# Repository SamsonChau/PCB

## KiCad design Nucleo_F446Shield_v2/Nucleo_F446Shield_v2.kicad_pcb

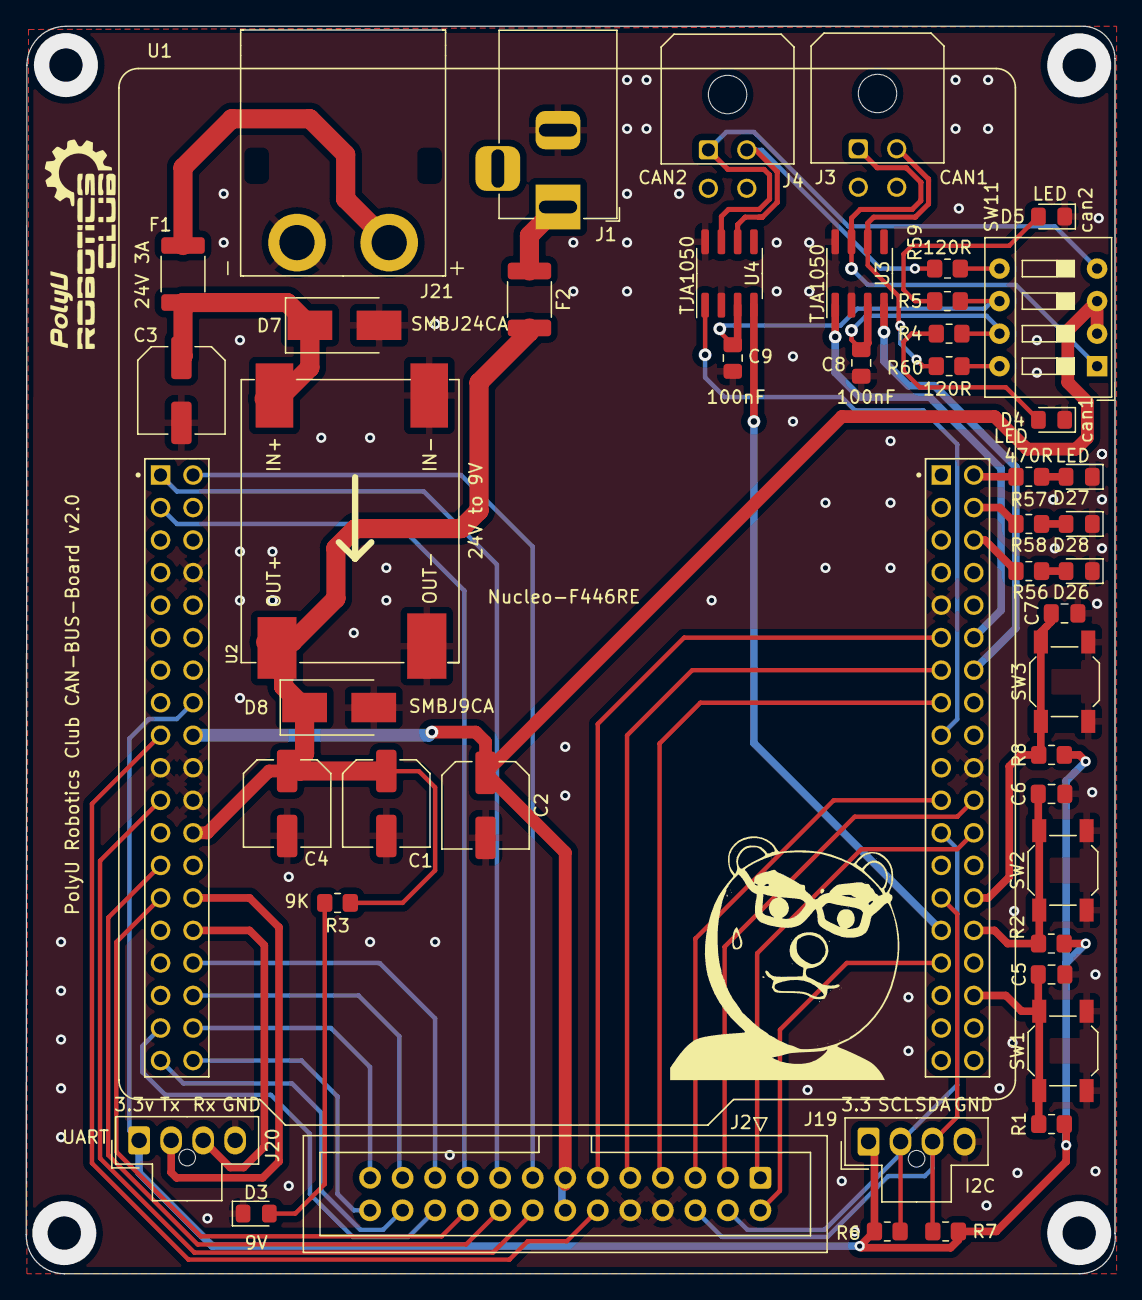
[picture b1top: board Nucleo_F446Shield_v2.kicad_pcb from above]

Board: 2 copper layers, 85.0 x 97.4 mm, 47 parts (0 on the bottom side), 55 nets.

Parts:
C1: 16v100uF; C_Elec_6.3x7.7
C2: 16v 47uF; C_Elec_6.3x7.7
C3: 35v 47uF; C_Elec_6.3x7.7
C4: 16v 100uF; C_Elec_6.3x7.7
C5, C6, C7, C8, C9: 100nF; C_0805_2012Metric_Pad1.18x1.45mm_HandSolder
D3: power_led; LED_0805_2012Metric_Pad1.15x1.40mm_HandSolder
D4: can_led; LED_0805_2012Metric_Pad1.15x1.40mm_HandSolder
D5: can2_led; LED_0805_2012Metric_Pad1.15x1.40mm_HandSolder
D7: SMBJ24CA; D_SMB_Handsoldering
D8: SMBJ9VCA; D_SMB_Handsoldering
D26: LED1; LED_0805_2012Metric_Pad1.15x1.40mm_HandSolder
D27: LED2; LED_0805_2012Metric_Pad1.15x1.40mm_HandSolder
D28: LED3; LED_0805_2012Metric_Pad1.15x1.40mm_HandSolder
F1, F2: 24V 3A; Fuse_1812_4532Metric_Pad1.30x3.40mm_HandSolder
J1: Barrel_Jack; BarrelJack_Horizontal
J2: Conn_02x13_Odd_Even; IDC-Header_2x13_P2.54mm_Vertical
J3: CAN1; Molex_Micro-Fit_3.0_43045-0400_2x02_P3.00mm_Horizontal
J4: CAN2; Molex_Micro-Fit_3.0_43045-0400_2x02_P3.00mm_Horizontal
J19: I2C3; Molex_Nano-Fit_105309-xx04_1x04_P2.50mm_Vertical
J20: UART4; Molex_Nano-Fit_105309-xx04_1x04_P2.50mm_Vertical
J21: xt60 male; XT60PW-M20
R1, R2, R8: 47k; R_0805_2012Metric_Pad1.20x1.40mm_HandSolder
R3, R4, R5: 10K; R_0805_2012Metric_Pad1.20x1.40mm_HandSolder
R6, R7: 4.7k; R_0805_2012Metric_Pad1.20x1.40mm_HandSolder
R56, R57, R58: 470R; R_0805_2012Metric_Pad1.20x1.40mm_HandSolder
R59, R60: 120R; R_0805_2012Metric_Pad1.20x1.40mm_HandSolder
SW1: SW1; SW_SPST_SKQG_WithoutStem
SW2: SW2; SW_SPST_SKQG_WithoutStem
SW3: SW3; SW_SPST_SKQG_WithoutStem
SW11: DIP1; SW_DIP_SPSTx04_Slide_9.78x12.34mm_W7.62mm_P2.54mm
U1: NUCLEO-F446RE
U2: MP1584; DC-DC-mp1584_module
U3, U4: TJA1050; SOIC-8_3.9x4.9mm_P1.27mm

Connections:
+3V3: J19.1, J20.1, R1.2, R2.2, R6.1, R7.1, R8.2, U1.CN7_16 (CN7_+3V3)
+5V: C2.1, J2.13, J2.14, SW11.2, SW11.3, U1.CN7_18 (CN7_+5V)
+24V: F1.1, J21.2
/CAN1+: J3.1, SW11.1, U3.7 (CANH)
/CAN1-: J3.2, R60.2, U3.6 (CANL)
/CAN1_VCC: C8.1, R4.1, SW11.7, U3.3 (VDD)
/CAN2+: J4.1, SW11.4, U4.7 (CANH)
/CAN2-: J4.2, R59.2, U4.6 (CANL)
/CAN2_VCC: C9.1, R5.1, SW11.6, U4.3 (VDD)
/PA0: J20.2, U1.CN7_28 (PA0)
/PA1: J20.3, U1.CN7_30 (PA1)
/PA8: J2.4, J19.2, R6.2, U1.CN10_23 (PA8)
/PA11: U1.CN10_14 (PA11), U3.4 (RXD)
/PA12: U1.CN10_12 (PA12), U3.1 (TXD)
/PB4: J2.6, J19.3, R7.2, U1.CN10_27 (PB4)
/PB5: U1.CN10_29 (PB5), U4.4 (RXD)
/PB6: U1.CN10_17 (PB6), U4.1 (TXD)
/PB13: C6.1, R2.1, SW2.2, U1.CN10_30 (PB13)
/PB14: C7.1, R8.1, SW3.2, U1.CN10_28 (PB14)
/PC4: C5.1, R1.1, SW1.2, U1.CN10_34 (PC4)
/PC5: R56.1, U1.CN10_6 (PC5)
/PC6: R58.1, U1.CN10_4 (PC6)
/PC8: R57.1, U1.CN10_2 (PC8)
GND: C1.2, C2.2, C3.2, C4.2, C5.2, C6.2, C7.2, C8.2, C9.2, D3.1 (K), D4.1 (K), D5.1 (K), D7.2 (A), D8.2 (A), D26.1 (K), D27.1 (K), D28.1 (K), J1.2, J2.8, J2.10, J19.4, J20.4, J21.1, SW1.1, SW2.1, SW3.1, U1.CN7_8 (CN7_GND), U1.CN7_19 (CN7_GND), U1.CN7_20 (CN7_GND), U1.CN7_22 (CN7_GND), U1.CN10_9 (CN10_GND), U1.CN10_20 (CN10_GND), U2.IN2- (VIN-), U2.OUT2- (VOUT-), U3.2 (VSS), U3.8 (Rs), U4.2 (VSS), U4.8 (Rs)
unnamed: C3.1, D7.1 (K), F1.2, U2.IN1+ (VIN+)
unnamed: D3.2 (A), R3.2
unnamed: D4.2 (A), R4.2
unnamed: D5.2 (A), R5.2
unnamed: D26.2 (A), R56.2
unnamed: D27.2 (A), R57.2
unnamed: D28.2 (A), R58.2
unnamed: F2.1, J1.1
unnamed: R59.1, SW11.5
unnamed: R60.1, SW11.8
PA4: J2.21, U1.CN7_32 (PA4)
PA5: J2.11, U1.CN10_11 (PA5)
PA6: J2.9, U1.CN10_13 (PA6)
PA7: J2.7, U1.CN10_15 (PA7)
PA9: J2.5, U1.CN10_21 (PA9)
PA15: J2.12, U1.CN7_17 (PA15)
PB0: J2.23, U1.CN7_34 (PB0)
PB1: J2.1, U1.CN10_24 (PB1)
PB2: J2.3, U1.CN10_22 (PB2)
PB3: J2.2, U1.CN10_31 (PB3)
PB7: J2.16, U1.CN7_21 (PB7)
PC0: J2.26, U1.CN7_38 (PC0/PB8)
PC1: J2.25, U1.CN7_36 (PC1/PB9)
PC2: J2.22, U1.CN7_35 (PC2)
PC3: J2.24, U1.CN7_37 (PC3)
PC10: J2.17, U1.CN7_1 (PC10)
PC11: J2.15, U1.CN7_2 (PC11)
PC12: J2.19, U1.CN7_3 (PC12)
PC14: J2.18, U1.CN7_25 (PC14)
PC15: J2.20, U1.CN7_27 (PC15)
VCC: C1.1, C4.1, D8.1 (K), F2.2, R3.1, U1.CN7_24 (CN7_VIN), U2.OUT1+ (VOUT+)

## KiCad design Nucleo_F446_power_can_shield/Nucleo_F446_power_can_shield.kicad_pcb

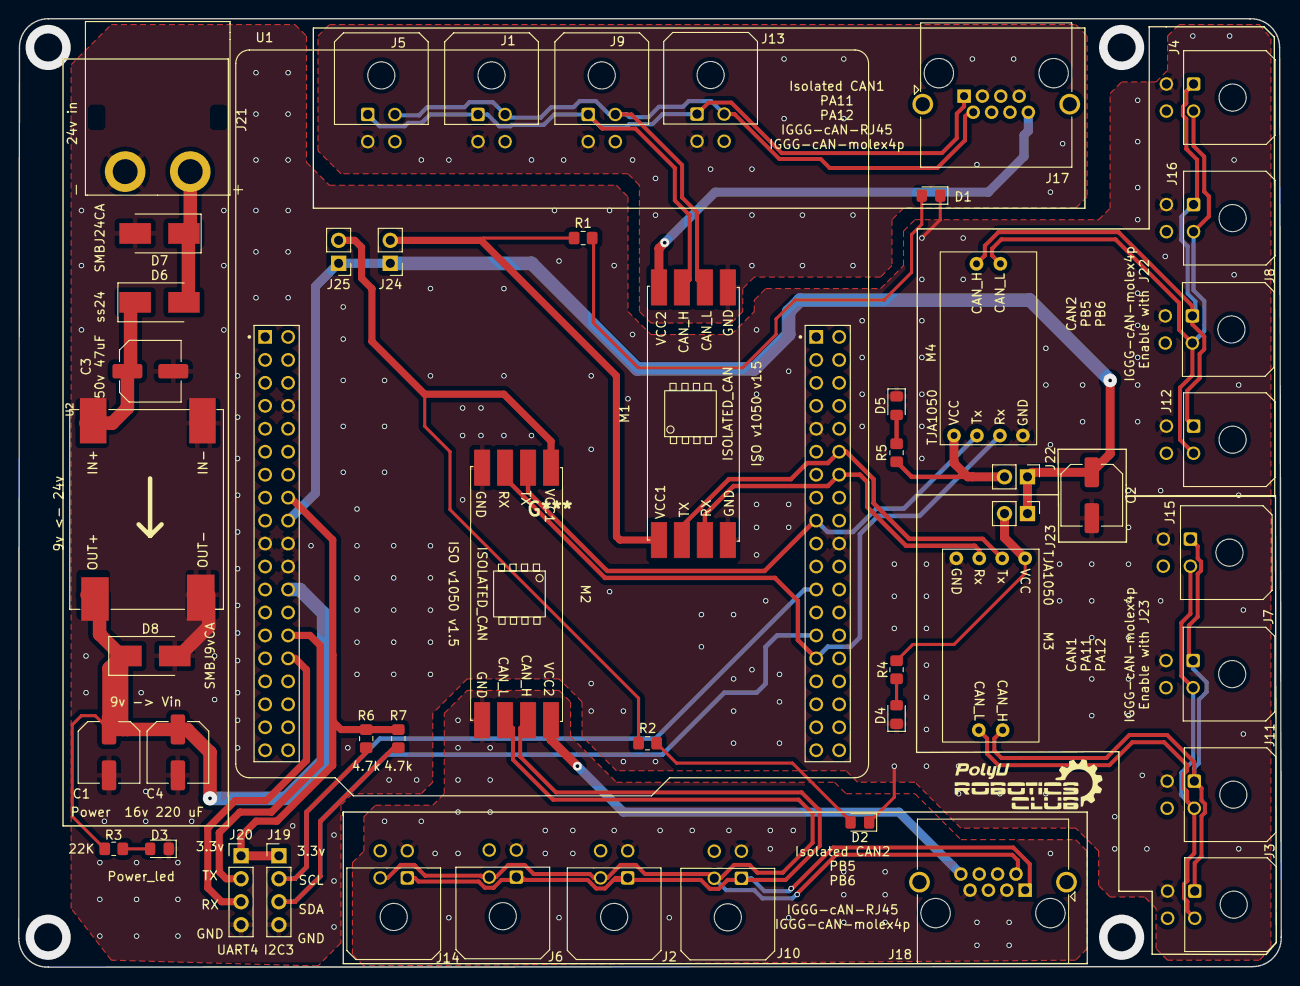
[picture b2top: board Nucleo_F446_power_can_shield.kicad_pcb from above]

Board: 2 copper layers, 139.7 x 104.9 mm, 50 parts (0 on the bottom side), 34 nets.

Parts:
C1: 16v220uF; C_Elec_6.3x7.7
C2, C4: 16v 220uF; C_Elec_6.3x7.7
C3: 50v 47uF; C_Elec_6.3x7.7
D1, D2, D4, D5: can_led; LED_0805_2012Metric_Pad1.15x1.40mm_HandSolder
D3: power_led; LED_0805_2012Metric_Pad1.15x1.40mm_HandSolder
D6: ss24; D_SMB_Handsoldering
D7: SMBJ24CA; D_SMB_Handsoldering
D8: SMBJ9VCA; D_SMB_Handsoldering
J1, J5, J9, J13: ISOCAN1; Molex_Micro-Fit_3.0_43045-0400_2x02_P3.00mm_Horizontal
J2, J6, J10, J14: ISOCAN2; Molex_Micro-Fit_3.0_43045-0400_2x02_P3.00mm_Horizontal
J3, J7, J11, J15: CAN1; Molex_Micro-Fit_3.0_43045-0400_2x02_P3.00mm_Horizontal
J4, J8, J12, J16: CAN2; Molex_Micro-Fit_3.0_43045-0400_2x02_P3.00mm_Horizontal
J17, J18: RJ45; RJ45_Amphenol_RJHSE5380
J19: I2C3; PinHeader_1x04_P2.54mm_Vertical
J20: UART4; PinHeader_1x04_P2.54mm_Vertical
J21: xt60 male; XT60PW-M20
J22, J23, J24, J25: enable; PinHeader_1x02_P2.54mm_Vertical
M1, M2: Isolated-Can-Transceiver-Module-ISO1050-Module
M3, M4: TJA1050_Module; TJA1050_CAN_Module
R1, R2, R4, R5: 10K; R_0805_2012Metric_Pad1.20x1.40mm_HandSolder
R3: 22K; R_0805_2012Metric_Pad1.20x1.40mm_HandSolder
R6, R7: 4.7k; R_0805_2012Metric_Pad1.20x1.40mm_HandSolder
U1: NUCLEO-F446RE
U2: MP1584; DC-DC-mp1584_module

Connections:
+3V3: J19.1, J20.1, R6.1, R7.1, U1.CN7_16 (CN7_+3V3)
+5V: C2.1, J22.1, J23.1, J24.1, J25.1, U1.CN7_18 (CN7_+5V)
+24V: D6.2 (A), D7.1 (K), J21.2
/CAN1+: J3.1, J7.1, J11.1, J15.1, M3.5 (CAN_H)
/CAN1-: J3.2, J7.2, J11.2, J15.2, M3.6 (CAN_L)
/CAN2+: J4.1, J8.1, J12.1, J16.1, M4.5 (CAN_H)
/CAN2-: J4.2, J8.2, J12.2, J16.2, M4.6 (CAN_L)
/ISO-CAN1+: J1.1, J5.1, J9.1, J13.1, J17.1, M1.6 (CAN_H)
/ISO-CAN1-: J1.2, J5.2, J9.2, J13.2, J17.2, M1.7 (CAN_L)
/ISO-CAN2+: J2.1, J6.1, J10.1, J14.1, J18.1, M2.6 (CAN_H)
/ISO-CAN2-: J2.2, J6.2, J10.2, J14.2, J18.2, M2.7 (CAN_L)
/PA0: J20.2, U1.CN7_28 (PA0)
/PA1: J20.3, U1.CN7_30 (PA1)
/PA8: J19.2, R6.2, U1.CN10_23 (PA8)
/PA11: M1.3 (RX), M3.3 (RX), U1.CN10_14 (PA11)
/PA12: M1.2 (TX), M3.2 (TX), U1.CN10_12 (PA12)
/PB4: J19.3, R7.2, U1.CN10_27 (PB4)
/PB5: M2.3 (RX), M4.3 (RX), U1.CN10_29 (PB5)
/PB6: M2.2 (TX), M4.2 (TX), U1.CN10_17 (PB6)
<NO NET>: J17.8, J18.8, M1.5 (VCC2), M2.5 (VCC2)
GND: C1.2, C2.2, C3.2, C4.2, D1.1 (K), D2.1 (K), D3.1 (K), D4.1 (K), D5.1 (K), D7.2 (A), D8.2 (A), J3.3, J4.3, J7.3, J8.3, J11.3, J12.3, J15.3, J16.3, J19.4, J20.4, J21.1, M1.4 (GND1), M2.4 (GND1), M3.4 (GND), M4.4 (GND), U1.CN7_8 (CN7_GND), U1.CN7_19 (CN7_GND), U1.CN7_20 (CN7_GND), U1.CN7_22 (CN7_GND), U1.CN10_9 (CN10_GND), U1.CN10_20 (CN10_GND), U2.IN2- (VIN-), U2.OUT2- (VOUT-)
GND1: J1.3, J5.3, J9.3, J13.3, J17.3, J17.7, M1.8 (GND2)
GND2: J2.3, J6.3, J10.3, J14.3, J18.3, J18.7, M2.8 (GND2)
unnamed: C3.1, D6.1 (K), U2.IN1+ (VIN+)
unnamed: D1.2 (A), R1.2
unnamed: D2.2 (A), R2.2
unnamed: D3.2 (A), R3.2
unnamed: D4.2 (A), R4.2
unnamed: D5.2 (A), R5.2
unnamed: J22.2, M4.1 (VCC), R5.1
unnamed: J23.2, M3.1 (VCC), R4.1
unnamed: J24.2, M1.1 (VCC1), R1.1
unnamed: J25.2, M2.1 (VCC1), R2.1
VCC: C1.1, C4.1, D8.1 (K), R3.1, U1.CN7_24 (CN7_VIN), U2.OUT1+ (VOUT+)

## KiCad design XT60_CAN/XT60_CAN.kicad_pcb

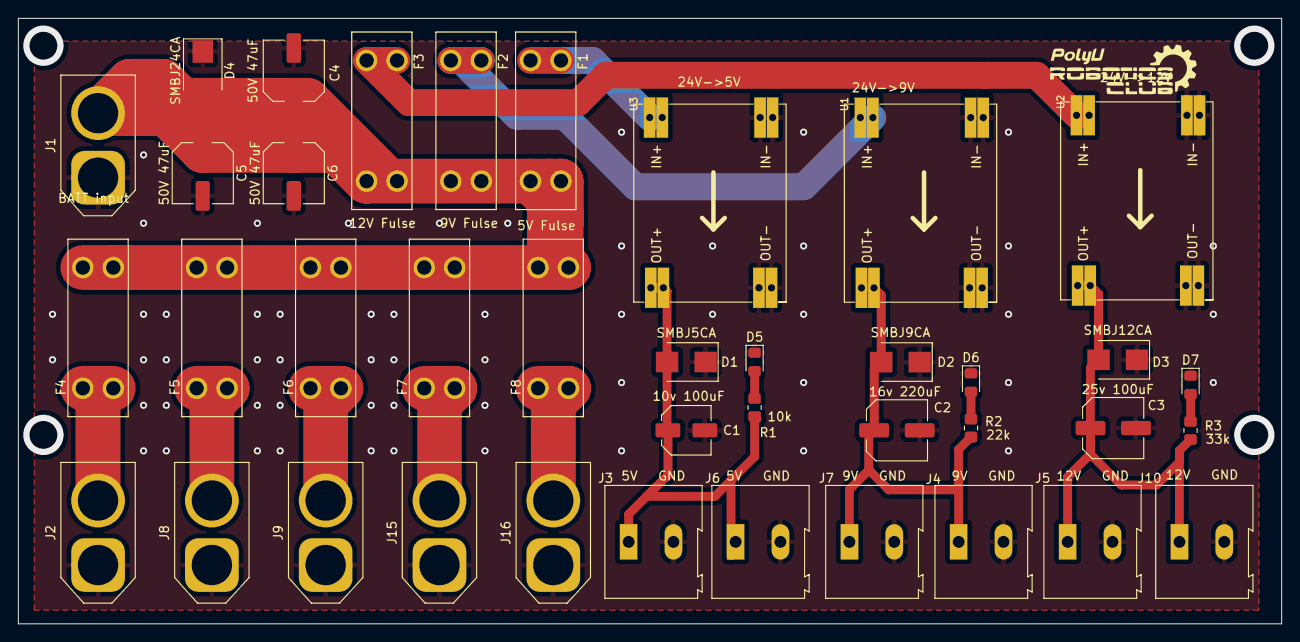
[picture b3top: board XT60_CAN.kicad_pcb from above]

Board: 2 copper layers, 141.0 x 67.6 mm, 39 parts (0 on the bottom side), 16 nets.

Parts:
C1: 10v 100uF; C_Elec_5x5.4
C2: 16v 220uF; C_Elec_6.3x7.7
C3: 25v 100uF; C_Elec_6.3x7.7
C4, C5, C6: 50v 47uF; C_Elec_6.3x7.7
D1: SMBJ5CA; D_SMB
D2: SMBJ9CA; D_SMB
D3: SMBJ12CA; D_SMB
D4: SMBJ24CA; D_SMB
D5: 5v_led; LED_0805_2012Metric_Pad1.15x1.40mm_HandSolder
D6: 9v_led; LED_0805_2012Metric_Pad1.15x1.40mm_HandSolder
D7: 12v_led; LED_0805_2012Metric_Pad1.15x1.40mm_HandSolder
F1, F2, F3, F4, F5, F6, F7, F8: 3557-2; FUSE_3557-2
J1: XT60_IN; AMASS_XT60-M_1x02_P7.20mm_Vertical
J2: XT60_CH1; AMASS_XT60-F_1x02_P7.20mm_Vertical
J3, J6: +5v; TerminalBlock_Altech_AK300-2_P5.00mm
J4, J7: +9v; TerminalBlock_Altech_AK300-2_P5.00mm
J5, J10: +12v; TerminalBlock_Altech_AK300-2_P5.00mm
J8: XT60_CH2; AMASS_XT60-F_1x02_P7.20mm_Vertical
J9: XT60_CH3; AMASS_XT60-F_1x02_P7.20mm_Vertical
J15: XT60_CH4; AMASS_XT60-F_1x02_P7.20mm_Vertical
J16: XT60_CH5; AMASS_XT60-F_1x02_P7.20mm_Vertical
R1: 10k; R_0805_2012Metric_Pad1.20x1.40mm_HandSolder
R2: 22k; R_0805_2012Metric_Pad1.20x1.40mm_HandSolder
R3: 33k; R_0805_2012Metric_Pad1.20x1.40mm_HandSolder
U1, U2, U3: MP1584; DC-DC-mp1584_module

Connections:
+5V: C1.1, D1.2 (A2), J3.1, J6.1, R1.1, U3.OUT1+ (VOUT+), U3.OUT2+ (VOUT+)
+9V: C2.1, D2.2 (A2), J4.1, J7.1, R2.1, U1.OUT1+ (VOUT+), U1.OUT2+ (VOUT+)
+12V: C3.1, D3.2 (A2), J5.1, J10.1, R3.1, U2.OUT1+ (VOUT+), U2.OUT2+ (VOUT+)
+24V: C4.1, C5.1, C6.1, D4.2 (A2), F1.2, F2.2, F3.2, F4.2, F5.2, F6.2, F7.2, F8.2, J1.2
GND: C1.2, C2.2, C3.2, C4.2, C5.2, C6.2, D1.1 (A1), D2.1 (A1), D3.1 (A1), D4.1 (A1), D5.1 (K), D6.1 (K), D7.1 (K), J1.1, J2.1, J3.2, J4.2, J5.2, J6.2, J7.2, J8.1, J9.1, J10.2, J15.1, J16.1, U1.IN1- (VIN-), U1.IN2- (VIN-), U1.OUT1- (VOUT-), U1.OUT2- (VOUT-), U2.IN1- (VIN-), U2.IN2- (VIN-), U2.OUT1- (VOUT-), U2.OUT2- (VOUT-), U3.IN1- (VIN-), U3.IN2- (VIN-), U3.OUT1- (VOUT-), U3.OUT2- (VOUT-)
unnamed: D5.2 (A), R1.2
unnamed: D6.2 (A), R2.2
unnamed: D7.2 (A), R3.2
unnamed: F1.1, U3.IN1+ (VIN+), U3.IN2+ (VIN+)
unnamed: F2.1, U1.IN1+ (VIN+), U1.IN2+ (VIN+)
unnamed: F3.1, U2.IN1+ (VIN+), U2.IN2+ (VIN+)
unnamed: F4.1, J2.2
unnamed: F5.1, J8.2
unnamed: F6.1, J9.2
unnamed: F7.1, J15.2
unnamed: F8.1, J16.2

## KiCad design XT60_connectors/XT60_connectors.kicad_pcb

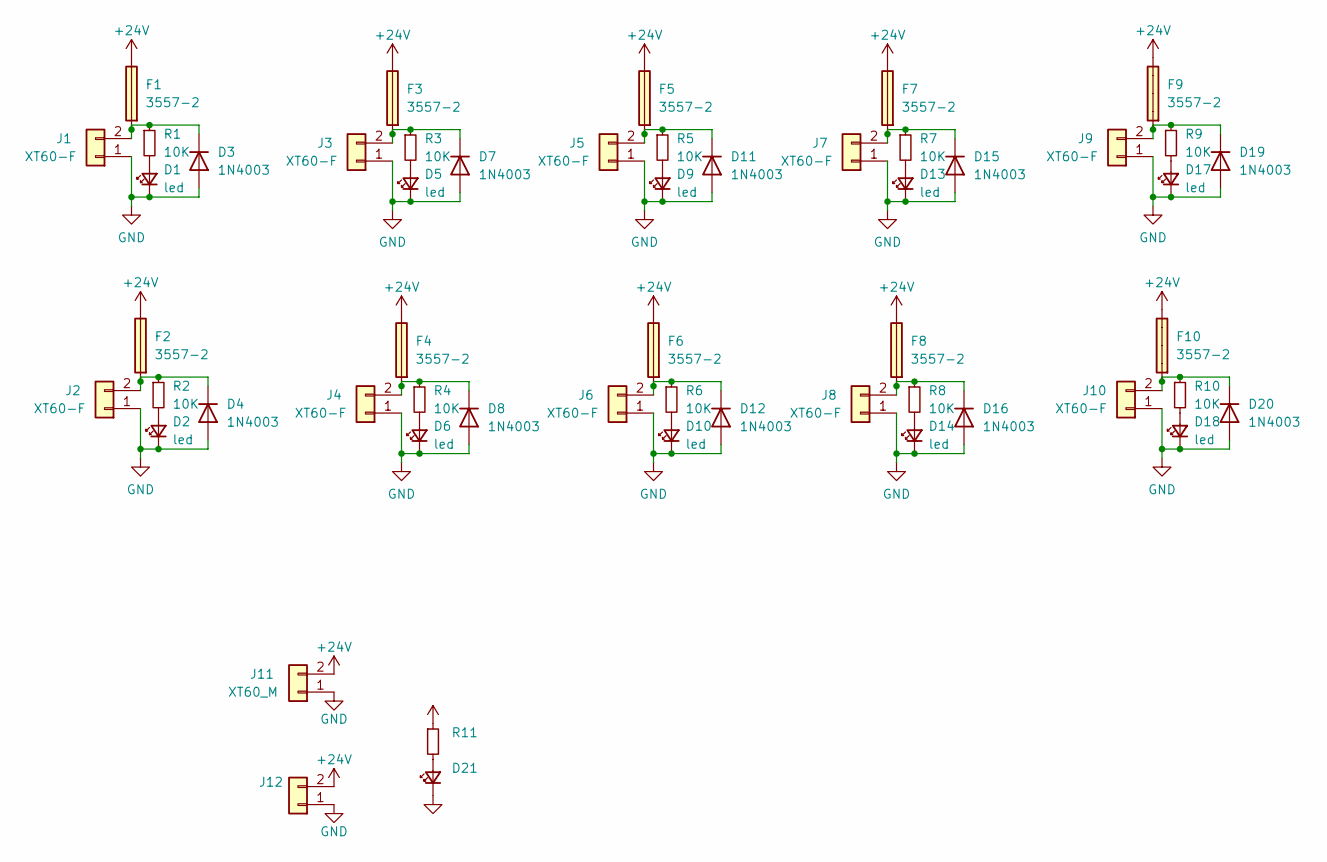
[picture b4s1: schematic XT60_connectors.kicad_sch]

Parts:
D1, D2, D5, D6, D9, D10, D13, D14, D17, D18: led; LED_0805_2012Metric_Pad1.15x1.40mm_HandSolder
D3, D4, D7, D8, D11, D12, D15, D16, D19, D20: 1N4003; D_DO-41_SOD81_P10.16mm_Horizontal
D21: (no value)
F1, F2, F3, F4, F5, F6, F7, F8, F9, F10: 3557-2; FUSE_3557-2
J1, J2, J3, J4, J5, J6, J7, J8, J9, J10: XT60-F; AMASS_XT60-F_1x02_P7.20mm_Vertical
J11: XT60_M; AMASS_XT60-M_1x02_P7.20mm_Vertical
J12: (no value)
R1, R2, R3, R4, R5, R6, R7, R8, R9, R10: 10K; R_0805_2012Metric_Pad1.20x1.40mm_HandSolder
R11: (no value)

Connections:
unnamed: D1.2 (A), R1.2
unnamed: D2.2 (A), R2.2
unnamed: D3.1 (K), F1.1, J1.2, R1.1
unnamed: D4.1 (K), F2.1, J2.2, R2.1
unnamed: D5.2 (A), R3.2
unnamed: D6.2 (A), R4.2
unnamed: D7.1 (K), F3.1, J3.2, R3.1
unnamed: D8.1 (K), F4.1, J4.2, R4.1
unnamed: D9.2 (A), R5.2
unnamed: D10.2 (A), R6.2
unnamed: D11.1 (K), F5.1, J5.2, R5.1
unnamed: D12.1 (K), F6.1, J6.2, R6.1
unnamed: D13.2 (A), R7.2
unnamed: D14.2 (A), R8.2
unnamed: D15.1 (K), F7.1, J7.2, R7.1
unnamed: D16.1 (K), F8.1, J8.2, R8.1
unnamed: D17.2 (A), R9.2
unnamed: D18.2 (A), R10.2
unnamed: D19.1 (K), F9.1, J9.2, R9.1
unnamed: D20.1 (K), F10.1, J10.2, R10.1
unnamed: D21.2 (A), R11.2

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
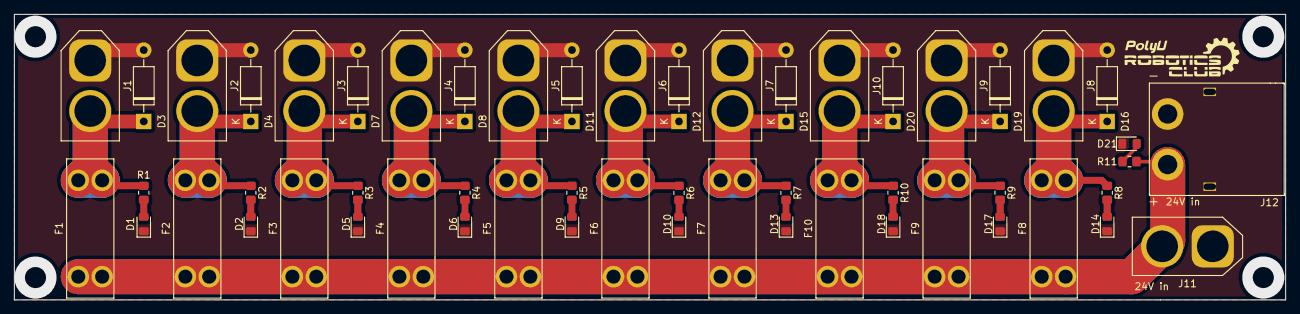
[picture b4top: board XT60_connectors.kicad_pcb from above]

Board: 2 copper layers, 181.0 x 40.6 mm, 54 parts (0 on the bottom side), 23 nets.

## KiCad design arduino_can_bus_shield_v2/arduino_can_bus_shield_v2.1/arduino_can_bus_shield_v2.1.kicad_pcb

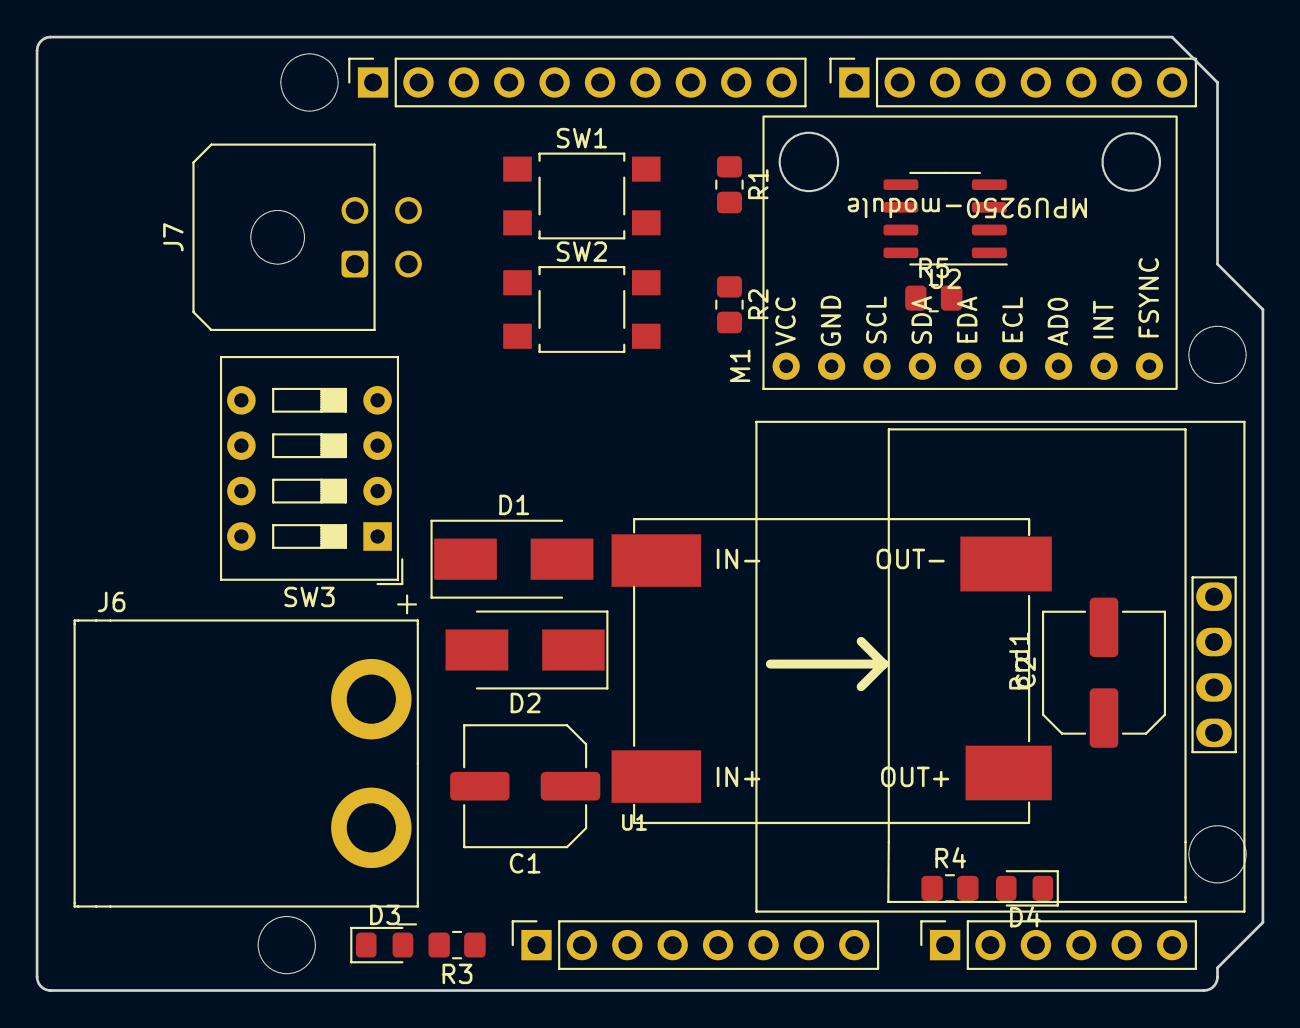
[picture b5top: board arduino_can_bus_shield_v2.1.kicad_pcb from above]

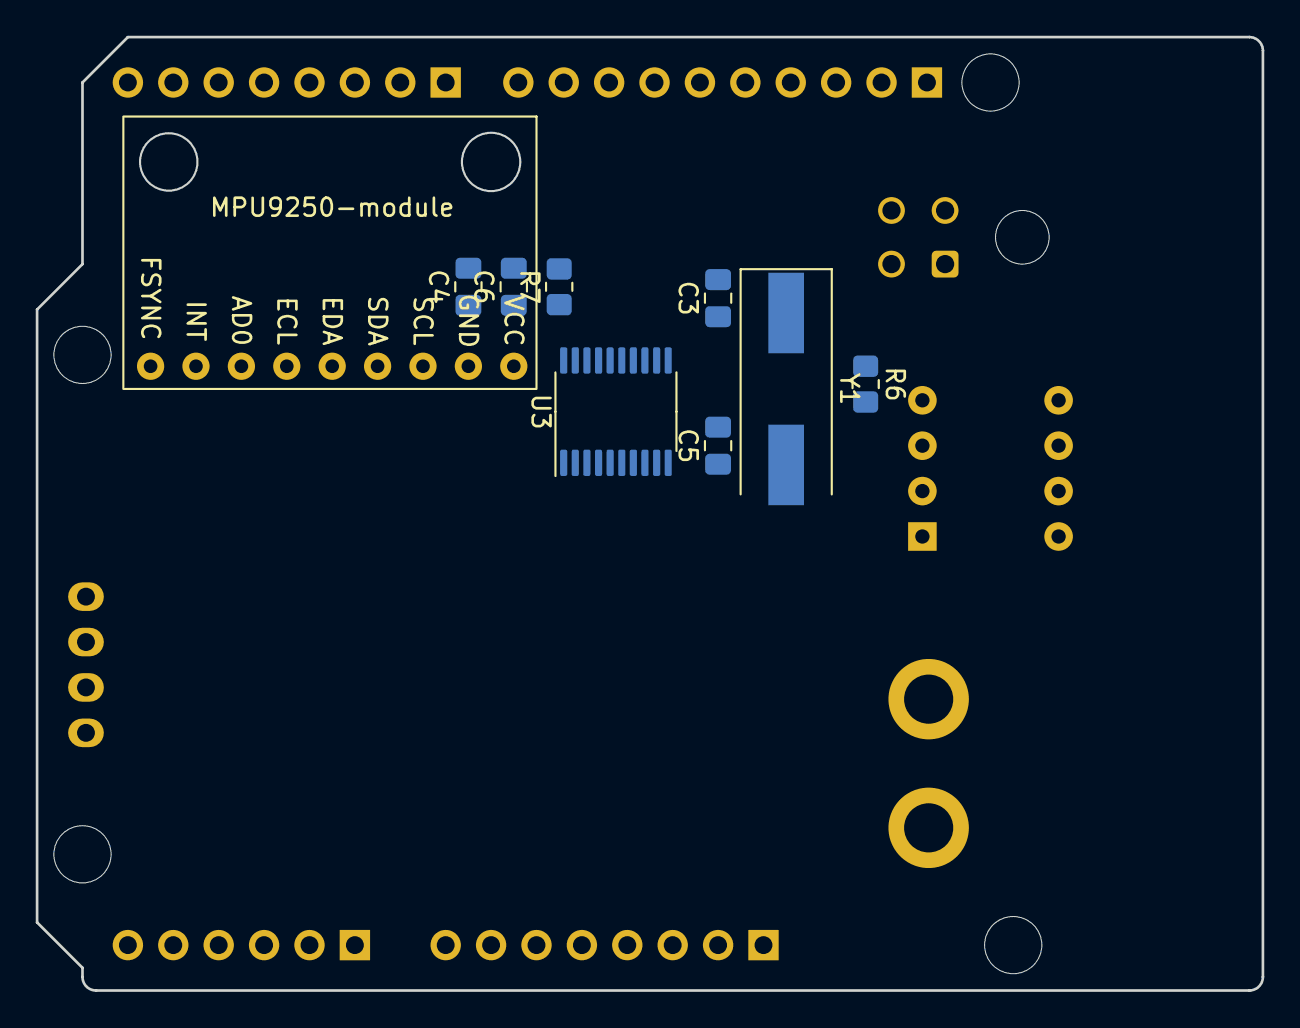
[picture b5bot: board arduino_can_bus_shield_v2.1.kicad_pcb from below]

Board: 2 copper layers, 68.6 x 53.3 mm, 36 parts (8 on the bottom side), 27 nets, no tracks yet.

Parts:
Brd1: SSD1306; 128x64OLED
C1: 50v 47uF; C_Elec_6.3x7.7
C2: 16v 220uF; C_Elec_6.3x7.7
C3, C5: 22pF; C_0805_2012Metric_Pad1.18x1.45mm_HandSolder
C4, C6: 100nF; C_0805_2012Metric_Pad1.18x1.45mm_HandSolder
D1: SMBJ24CA; D_SMB_Handsoldering
D2: ss24; D_SMB_Handsoldering
D3: power; LED_0805_2012Metric_Pad1.15x1.40mm_HandSolder
D4: user; LED_0805_2012Metric_Pad1.15x1.40mm_HandSolder
J1: Power; PinSocket_1x08_P2.54mm_Vertical
J2: Digital/PWM; PinSocket_1x10_P2.54mm_Vertical
J3: Analog; PinSocket_1x06_P2.54mm_Vertical
J4: Digital/PWM; PinSocket_1x08_P2.54mm_Vertical
J6: xt60 male; XT60PW-M20
J7: molex_3.0; Molex_Micro-Fit_3.0_43045-0400_2x02_P3.00mm_Horizontal
M1: MPU9250_module
MH1, MH2, MH3, MH4: MountingHole_3.2mm
R1, R2, R3, R4, R7: 10K; R_0805_2012Metric_Pad1.20x1.40mm_HandSolder
R5: 17K; R_0805_2012Metric_Pad1.20x1.40mm_HandSolder
R6: 120; R_0805_2012Metric_Pad1.20x1.40mm_HandSolder
SW1: User; SW_SPST_TL3305A
SW2: User; SW_SPST_TL3305C
SW3: SW_DIP_x04; SW_DIP_SPSTx04_Slide_9.78x12.34mm_W7.62mm_P2.54mm
U1: MP1584; DC-DC-mp1584_module
U2: MCP2551-I-SN; SOIC-8_3.9x4.9mm_P1.27mm
U3: MCP2515-xST; TSSOP-20_4.4x6.5mm_P0.65mm
Y1: 16MHz; Crystal_SMD_HC49-SD

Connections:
+5V: J1.5, R3.1, R7.1, SW1.2, SW2.2, SW3.1, SW3.2
+24V: D1.1 (K), D2.2 (A), J6.2
/7: J4.1, U3.18 (~CS)
/8: J2.10, R2.1, SW2.1
/9(**): R1.1, SW1.1
/A0: J3.1, R4.1
/A4(SDA): Brd1.4 (SDA), M1.3 (SDA)
/A5(SCL): Brd1.3 (SCL), M1.2 (SCL)
/CAN+: J7.1, R6.1, U2.7 (CANH)
/CAN-: J7.2, SW3.5, U2.6 (CANL)
/CAN_Rx: U2.4 (RXD), U3.2 (RXCAN)
/CAN_Tx: U2.1 (TXD), U3.1 (TXCAN)
/SCL/A5: J2.1, J3.6
/SDA/A4: J2.2, J3.5
/can_enable: C4.1, C6.1, SW3.8, U2.3 (VDD), U3.20 (VDD)
/imu_enable: M1.0 (VCC), SW3.7
GND: Brd1.1 (GND), C1.2, C2.2, C3.2, C4.2, C5.2, C6.2, D1.2 (A), D3.1 (K), D4.1 (K), J1.6, J1.7, J2.4, J6.1, M1.1 (GND), R1.2, R2.2, R5.2, SW3.6, U1.IN2- (VIN-), U1.OUT2- (VOUT-), U2.2 (VSS), U3.10 (VSS)
unnamed: C1.1, D2.1 (K), U1.IN2+ (VIN+)
unnamed: C3.1, U3.8 (OSC2), Y1.1
unnamed: C5.1, U3.9 (OSC1), Y1.2
unnamed: D3.2 (A), R3.2
unnamed: D4.2 (A), R4.2
unnamed: J7.3, SW3.3
unnamed: R5.1, U2.8 (Rs)
unnamed: R6.2, SW3.4
unnamed: R7.2, U3.19 (~RESET)
VCC: C2.1, J1.8, U1.OUT2+ (VOUT+)

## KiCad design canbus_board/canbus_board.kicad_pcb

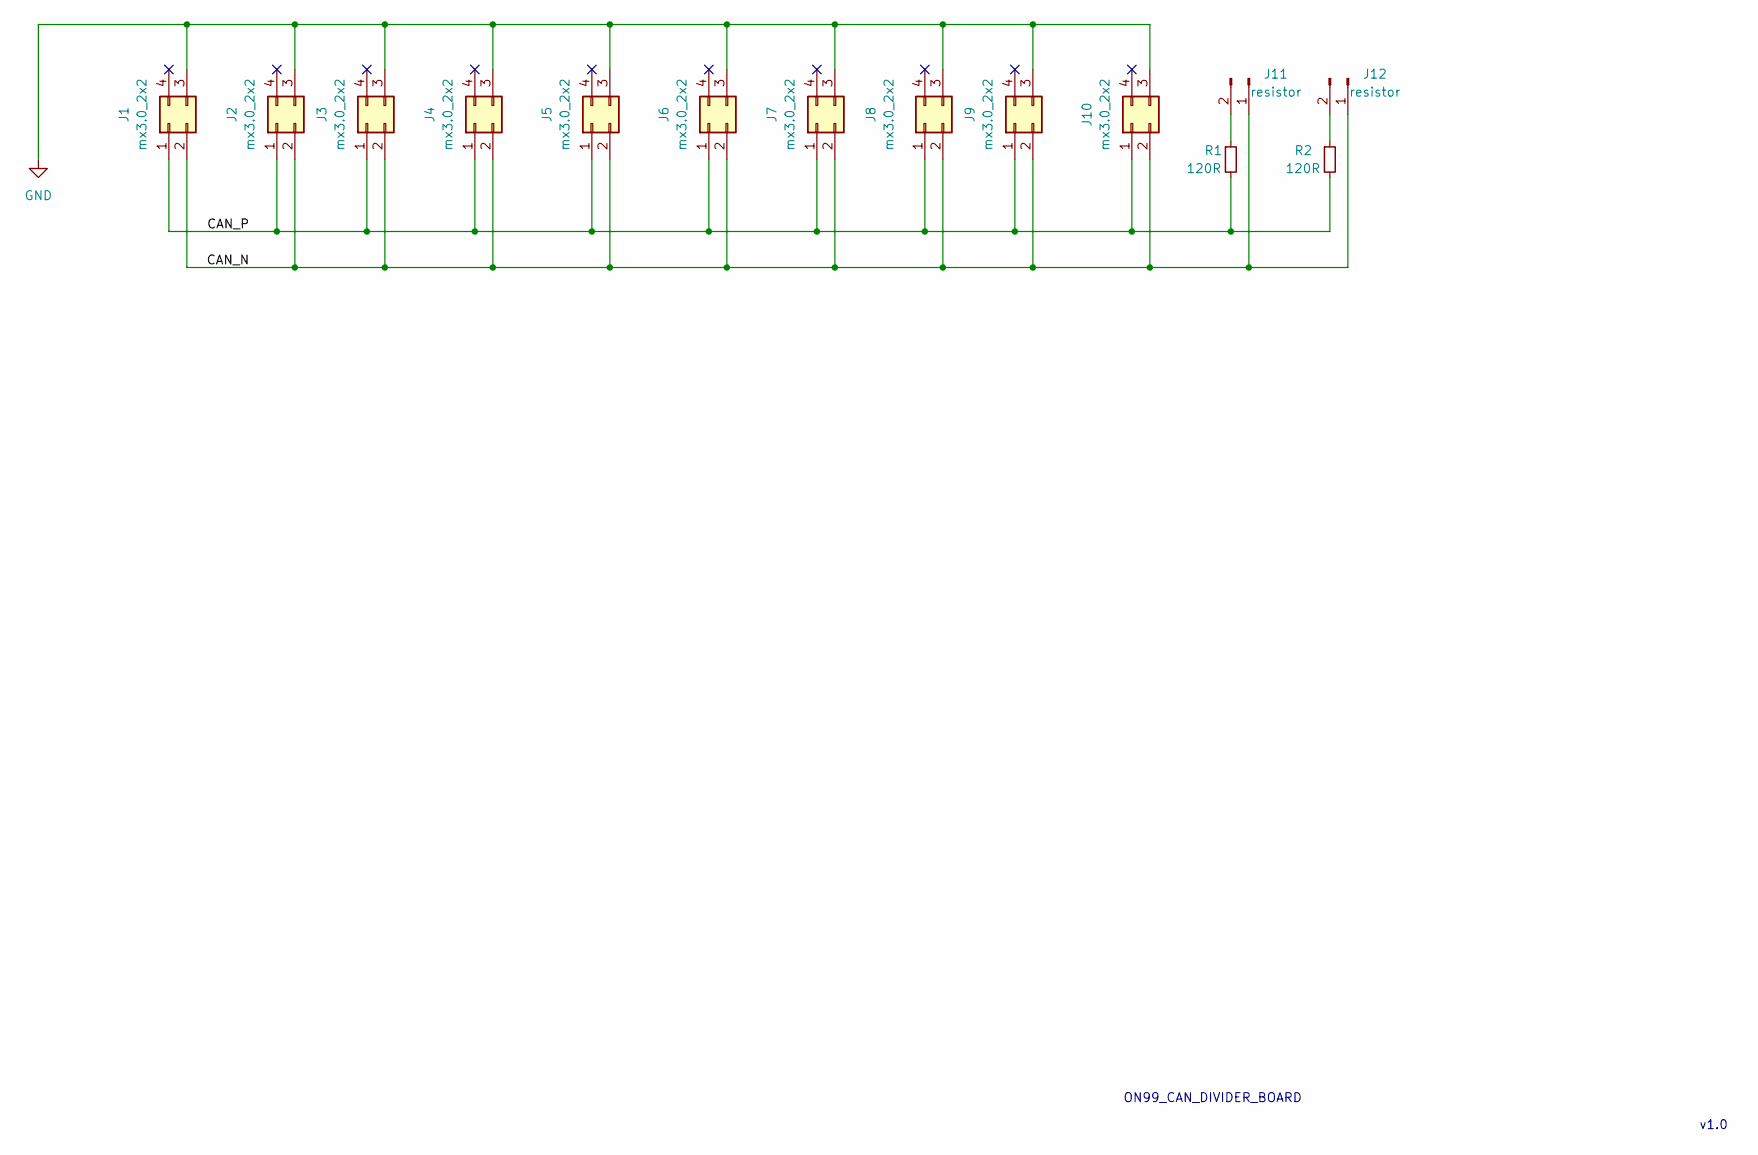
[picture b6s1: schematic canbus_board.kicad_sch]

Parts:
J1, J2, J3, J4, J5, J6, J7, J8, J9, J10: mx3.0_2x2; Molex_Micro-Fit_3.0_43045-0412_2x02_P3.00mm_Vertical
J11, J12: resistor; PinHeader_1x02_P2.54mm_Vertical
R1, R2: 120R; R_0805_2012Metric_Pad1.20x1.40mm_HandSolder

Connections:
/CAN_N: J1.2, J2.2, J3.2, J4.2, J5.2, J6.2, J7.2, J8.2, J9.2, J10.2, J11.1, J12.1
/CAN_P: J1.1, J2.1, J3.1, J4.1, J5.1, J6.1, J7.1, J8.1, J9.1, J10.1, R1.2, R2.2
GND: J1.3, J2.3, J3.3, J4.3, J5.3, J6.3, J7.3, J8.3, J9.3, J10.3
unnamed: J11.2, R1.1
unnamed: J12.2, R2.1

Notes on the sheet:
v1.0
ON99_CAN_DIVIDER_BOARD

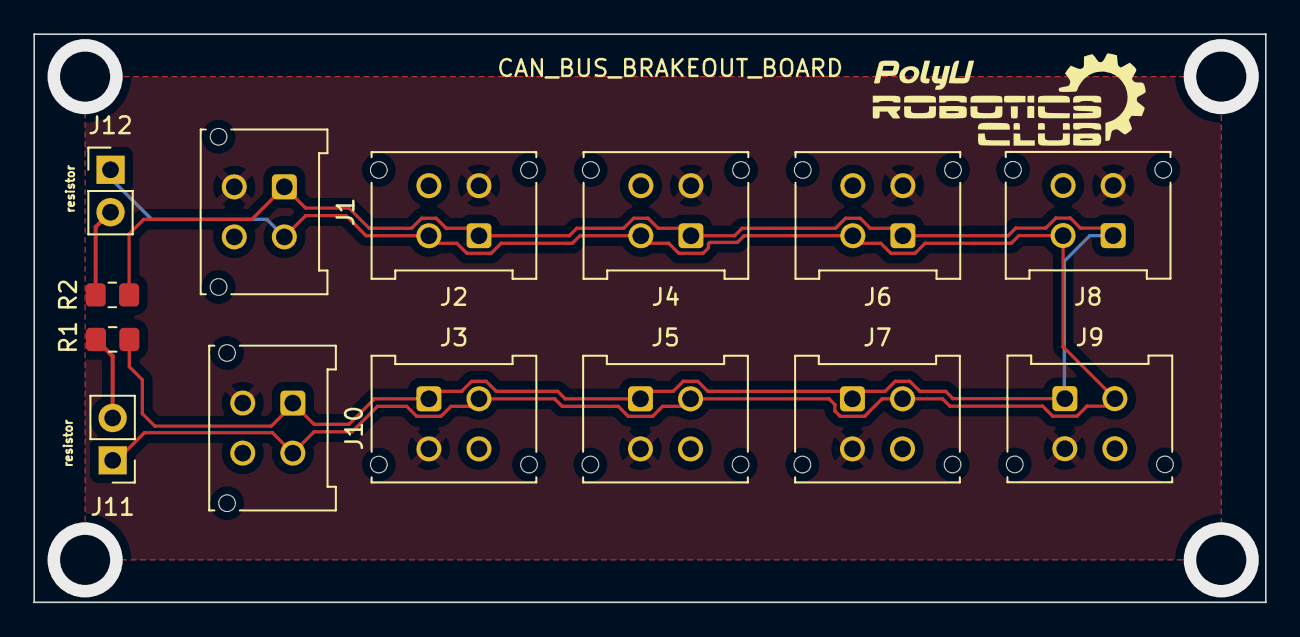
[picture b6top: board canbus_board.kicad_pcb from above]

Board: 2 copper layers, 73.8 x 34.0 mm, 14 parts (0 on the bottom side), 5 nets.
